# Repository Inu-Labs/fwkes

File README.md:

FWKES[^1] is an open-source NES emulator targeted at 32-bit microcontroller RP2350. It aims to be
precise and cycle-accurate, while still maintaining stable 60 FPS and minimal latency.

*TODO: add demonstration (video, screenshots)*

Features:

- SD card for storing games and files.
- HDMI for video output.
- 3.5mm audio jack for audio output.
- Supports raster effects (mid-scanline writes).
- Emulates NTSC region, i.e. original NES and Famicom (although support for PAL is planned).
- Implements all instruction set of Ricoh 2A03 (MOS 6502), including unofficial instructions and
precise timing.
- Implements all features of PPU (sprite overflow, emphasis bits, ...) and APU.
- Supports **NROM**, **MMC1**, **UNROM** and **MMC3** mappers.
- Supports RP2350-based boards **Raspberry Pi Pico 2**, **Pimoroni Pico Plus 2** and any compatible
board.
- FWKES comes with BIOS that delivers user-friendly interface for loading programs and
  configuration. BIOS can be freely reprogrammed, i.e. can replace it with their own program.
- To allow emulated programs make use of peripherals like SD card, or configure emulator's behavior,
  there is a bridge (hypercall interface) called FWX.

# Building

Although FWKES is aimed at RP2350-based boards, there are development builds for desktop. Desktop
uses SDL3 to handle video, audio and inputs, and it's intended for superficial testing of
non-RP2350-specific aspects.

There is also an ongoing development of debugger, which allows complex testing not only of FWKES
itself, but also emulated programs and games. It's code can be found in the `debugger` branch.

## Dependencies

For RP2350 based, you'll need [ARM GCC compiler toolchain with C11
support](https://developer.arm.com/downloads/-/arm-gnu-toolchain-downloads) and [extracted Pico
SDK](https://github.com/raspberrypi/pico-sdk).

For desktop and debugger versions, only [SDL3](https://www.libsdl.org/) is required to be installed
and usable by CMake. Both GCC and Clang are usable.

For general building, you'll also need [CMake](https://cmake.org/) and [Git](https://git-scm.com/).

Many of listed tools are available in distribution's repositories on Linux.

## Cloning

Since most dependencies are handled using Git submodules, you need to use `git clone --recurse-submodules
https://github.com/Inu-Labs/fwkes.git`. Alternatively, if you already cloned and submodules are not
initialized, you need to run `git submodule update --init --recursive --progress`.

## Raspberry Pi Pico 2

`-DBUILD_RP2350=ON` must be specified when compiling for official Pico 2:

```sh
mkdir build
cd build
cmake -DPICO_SDK_PATH=path_to_extracted_pico-sdk -DCMAKE_BUILD_TYPE=Release -GNinja -DBUILD_RP2350=ON ..
```

## Pimoroni Pico Plus 2

Both `-DBUILD_RP2350=ON` and `-DBUILD_PIMORONI2=ON` must be specified when compiling for Pimoroni 2:

```sh
mkdir build
cd build
cmake -DPICO_SDK_PATH=path_to_extracted_pico-sdk -DCMAKE_BUILD_TYPE=Release -GNinja -DBUILD_RP2350=ON -DBUILD_PIMORONI2=ON ..
```

## Desktop

Pass `-DBUILD_DESKTOP=ON`:

```sh
mkdir build
cd build
cmake -GNinja -DBUILD_DESKTOP=ON -DCMAKE_POLICY_VERSION_MINIMUM=3.5 ..
```

## Debugger

Pass both `-DBUILD_DESKTOP=ON` and `-DBUILD_DEBUGGER=ON`:

```sh
mkdir build
cd build
cmake -GNinja -DBUILD_DESKTOP=ON -DBUILD_DEBUGGER=ON -DCMAKE_POLICY_VERSION_MINIMUM=3.5 ..
```

## Tests (development only)

To build tests, pass `-DBUILD_TESTS=ON` and `-DBUILD_VISUAL_TESTS=ON`:

```sh
mkdir build
cd build
cmake -GNinja -DBUILD_DESKTOP=ON -DBUILD_TESTS=ON -DBUILD_VISUAL_TESTS=ON ..
```

`-DBUILD_VISUAL_TESTS=ON` is required for tests that depend on SDL3.

## Flashing firmware

To flash compiled firmware to RP2350 board, you can either:

- Copy `build/src/rp2350/fwkes-rp2350.uf2` to the board. Note that the board must be booted in the BOOTSEL mode to perform this (otherwise it will not even appear in your file manager).
- Use [picotool](https://github.com/raspberrypi/picotool): `picotool load build/src/rp2350/fwkes-rp2350.uf2 -f && picotool reboot`

A CMake rule for this is planned in the future.

## Electronics, case

*TODO*

# License & Acknowledgement

Code of FWKES is licensed under [GNU GPL v2.0](LICENSE.txt), while hardware (schematics, PCB designs
and 3D models) is licensed under [CERN Open Hardware Licence Version 2 (Strongly
Reciprocal)](./CERN-OHL-S-2.0-LICENSE.txt). This project is a collaborative work of
[inunix3](https://github.com/inunix3) and [kubaa-ma](https://github.com/kubaa-ma).

Software side of FWKES makes use of the following libraries:

- [pico-sdk](https://github.com/raspberrypi/pico-sdk) - not too low-level interaction with RP2350 peripherals.
- [PicoDVI](https://github.com/Wren6991/PicoDVI) - generation of bitbanged DVI signal.
- [LwMEM](https://github.com/MaJerle/lwmem) - allocator interface for embedded systems (used for PSRAM).
- [FatFS](https://elm-chan.org/fsw/ff/) - FAT filesystem implementation for SD card.
- [Unity](https://github.com/ThrowTheSwitch/Unity) - unit-testing framework (used for CPU tests).
- [ImGui](https://github.com/ocornut/imgui.git) and [imgui_club](https://github.com/ocornut/imgui_club.git) - used for debugger UI.
- [ImGuiFileDialog](https://github.com/aiekick/ImGuiFileDialog) - used for open/save file dialog in the debugger.

[^1]: FWKES is pronounced as fukes (/fʌkɛs/). In old Bible printings, you can find that sometimes
    letter U is written as V. So we took it further and doubled it! Although it's not read as double
    U...

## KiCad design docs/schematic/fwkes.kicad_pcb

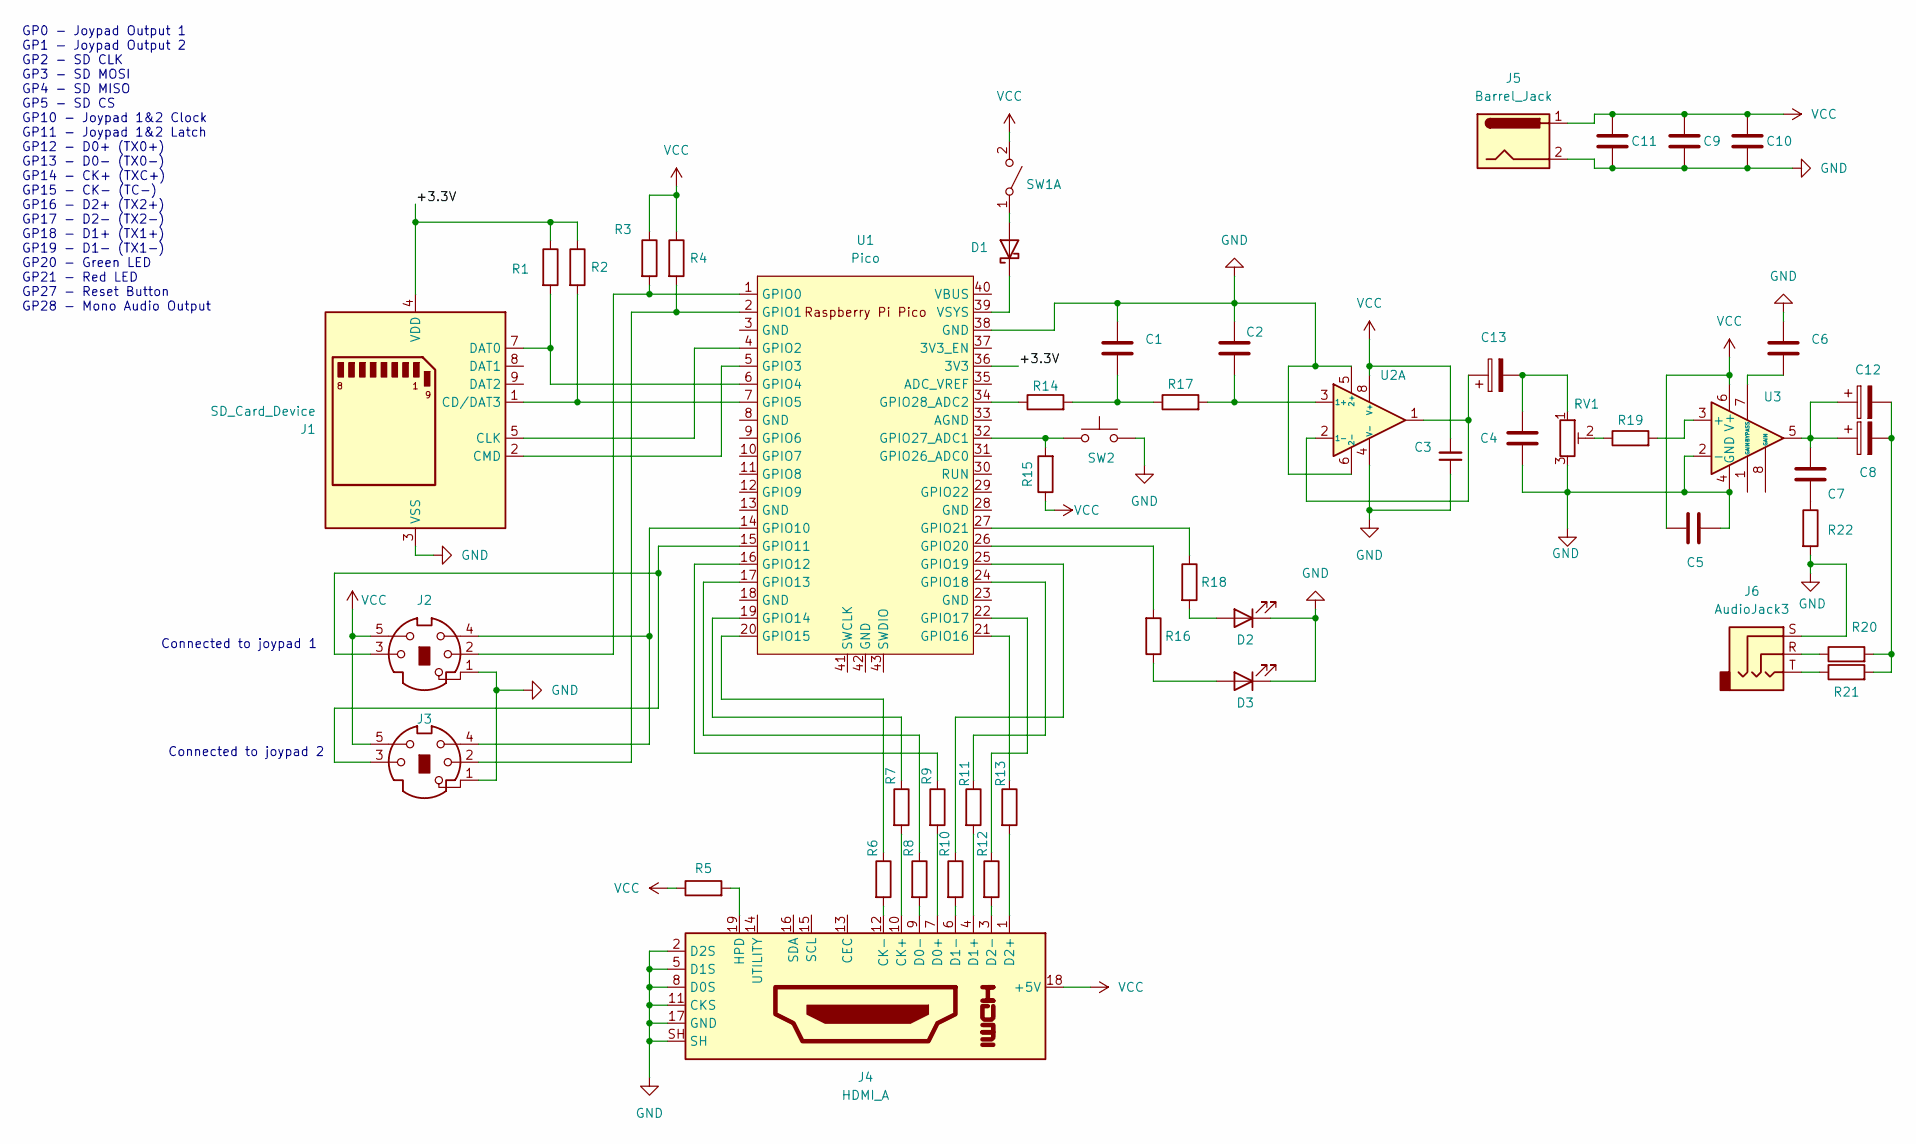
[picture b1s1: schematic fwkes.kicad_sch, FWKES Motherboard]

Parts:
C1, C2: 4n7; C_0603_1608Metric
C3, C4, C5, C6, C7: 100n; C_0603_1608Metric
C8, C10, C12: 100u; C_1210_3225Metric
C9, C13: 10u; C_0603_1608Metric
C11: 1u; C_0603_1608Metric
D1: D_Schottky; D_SOD-123
D2, D3: LED; LED_D3.0mm_Horizontal_O1.27mm_Z2.0mm
J1: SD_Card_Device; SD_Hirose_DM1AA_SF_PEJ82
J2, J3: Mini-DIN-5; MINI_DIN5_KMDGX_5S_BS
J4: HDMI_A; HDMI_A_Amphenol_10029449-x01xLF_Horizontal
J5: Barrel_Jack; BarrelJack_Horizontal
J6: AudioJack3; Jack_3.5mm_Lumberg_1503_03_Horizontal
R1, R2, R3, R4, R5, R15, R22: 10k; R_0603_1608Metric
R6, R7, R8, R9, R10, R11, R12, R13, R16, R18: 220; R_0603_1608Metric
R14, R17: 3k3; R_0603_1608Metric
R19, R20, R21: 1k; R_0603_1608Metric
RV1: 10k; Potentiometer_Bourns_3296Y_Vertical
SW1: SW_DPST_x2; SW_NKK_BB15AH
SW2: SW_Push; SW_NKK_BB15AH
U1: Pico; pico2_socket
U2: LM358; SOIC-8_3.9x4.9mm_P1.27mm
U3: LM386; SOIC-8_3.9x4.9mm_P1.27mm

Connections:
/+3.3V: J1.4 (VDD), R1.1, R2.1, U1.36 (3V3)
GND: C1.1, C2.1, C3.1, C4.2, C5.1, C6.1, C9.2, C10.2, C11.2, D2.1 (K), D3.1 (K), J1.3 (VSS), J1.6 (VSS), J2.1, J3.1, J4.2 (D2S), J4.5 (D1S), J4.8 (D0S), J4.11 (CKS), J4.17 (GND), J4.SH, J5.2, J6.S, R22.2, RV1.3, SW2.2, U1.38 (GND), U2.4 (V-), U2.5 (2+), U2.6 (2-), U3.2 (-), U3.4 (GND)
unnamed: C1.2, R14.2, R17.1
unnamed: C7.2, R22.1
unnamed: C7.1, C8.1, C12.1, U3.5
unnamed: C8.2, C12.2, R20.2, R21.2
unnamed: C4.1, C13.2, RV1.1
unnamed: D1.2 (A), SW1.1 (A)
unnamed: D1.1 (K), U1.39 (VSYS)
unnamed: D2.2 (A), R18.2
unnamed: J1.1 (CD/DAT3), R2.2, U1.7 (GPIO5)
unnamed: J1.5 (CLK), U1.4 (GPIO2)
unnamed: J1.2 (CMD), U1.5 (GPIO3)
unnamed: J1.7 (DAT0), R1.2, U1.6 (GPIO4)
unnamed: J4.10 (CK+), R7.2
unnamed: J4.12 (CK-), R6.2
unnamed: J4.7 (D0+), R9.2
unnamed: J4.9 (D0-), R8.2
unnamed: J4.4 (D1+), R11.2
unnamed: J4.6 (D1-), R10.2
unnamed: J4.1 (D2+), R13.2
unnamed: J4.3 (D2-), R12.2
unnamed: J4.19 (HPD), R5.2
unnamed: J6.R, R20.1
unnamed: J6.T, R21.1
unnamed: R19.1, RV1.2
unnamed: J2.2, R3.2, U1.1 (GPIO0)
unnamed: J3.2, R4.2, U1.2 (GPIO1)
unnamed: J2.4, J3.4, U1.14 (GPIO10)
unnamed: J2.3, J3.3, U1.15 (GPIO11)
unnamed: R9.1, U1.16 (GPIO12)
unnamed: R8.1, U1.17 (GPIO13)
unnamed: R7.1, U1.19 (GPIO14)
unnamed: R6.1, U1.20 (GPIO15)
unnamed: R13.1, U1.21 (GPIO16)
unnamed: R12.1, U1.22 (GPIO17)
unnamed: R11.1, U1.24 (GPIO18)
unnamed: R10.1, U1.25 (GPIO19)
unnamed: R18.1, U1.27 (GPIO21)
unnamed: R15.2, SW2.1, U1.32 (GPIO27_ADC1)
unnamed: R14.1, U1.34 (GPIO28_ADC2)
unnamed: C2.2, R17.2, U2.3 (1+)
unnamed: C13.1, U2.1, U2.2 (1-)
unnamed: R19.2, U3.3 (+)
unnamed: C6.2, U3.7 (BYPASS)
VCC: C3.2, C5.2, C9.1, C10.1, C11.1, J2.5, J3.5, J4.18 (+5V), J5.1, R3.1, R4.1, R5.1, R15.1, SW1.2 (B), U2.8 (V+), U3.6 (V+)

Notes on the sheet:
Connected to joypad 2
Connected to joypad 1
GP0 - Joypad Output 1 GP1 - Joypad Output 2 GP2 - SD CLK GP3 - SD MOSI GP4 - SD MISO GP5 - SD CS GP10 - Joypad 1&2 Clock GP11 - Joypad 1&2 Latch GP12 - D0+ (TX0+) GP13 - D0- (TX0-) GP14 - CK+ (TXC+) GP15 - CK- (TC-) GP16 - D2+ (TX2+) GP17 - D2- (TX2-) GP18 - D1+ (TX1+) GP19 - D1- (TX1-) GP20 - Gree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

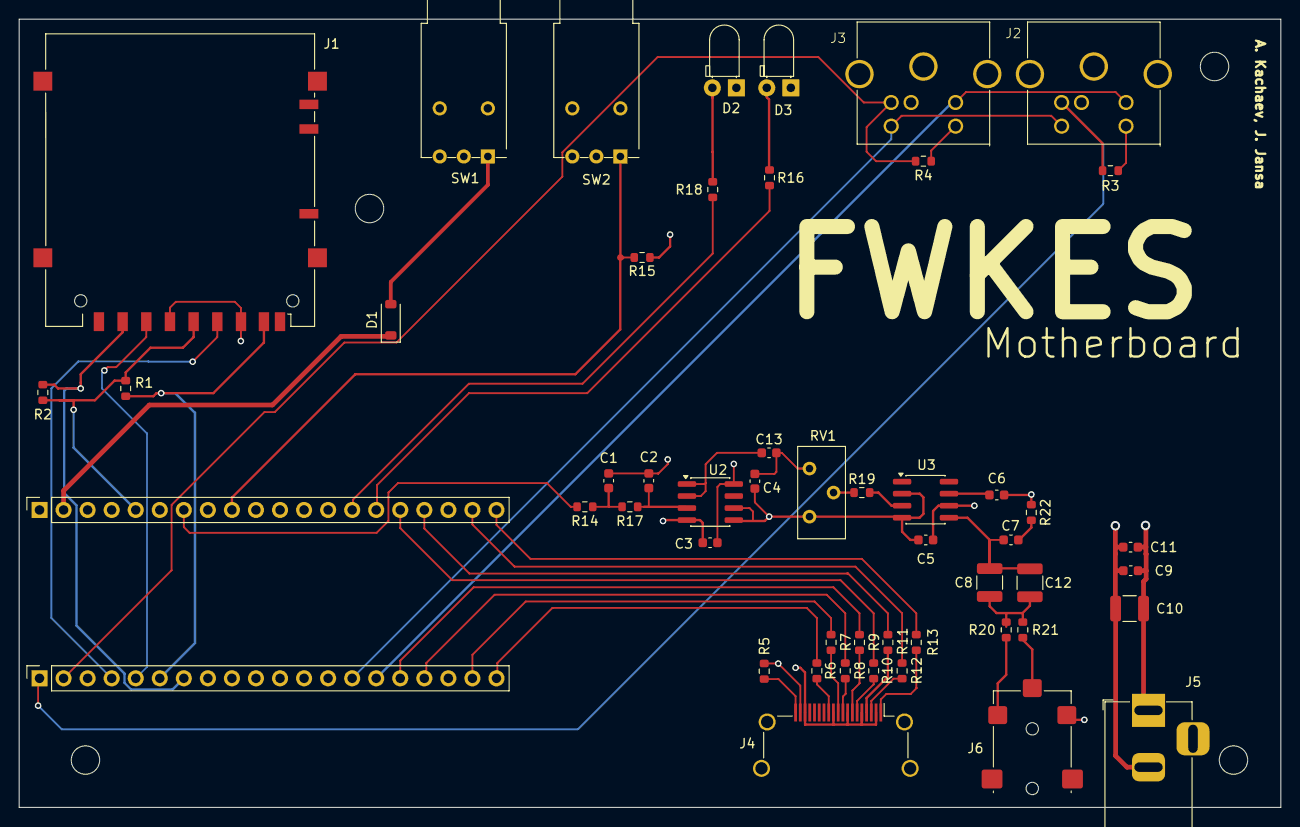
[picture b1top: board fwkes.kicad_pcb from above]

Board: 4 copper layers, 133.2 x 83.2 mm, 50 parts (0 on the bottom side), 48 nets.

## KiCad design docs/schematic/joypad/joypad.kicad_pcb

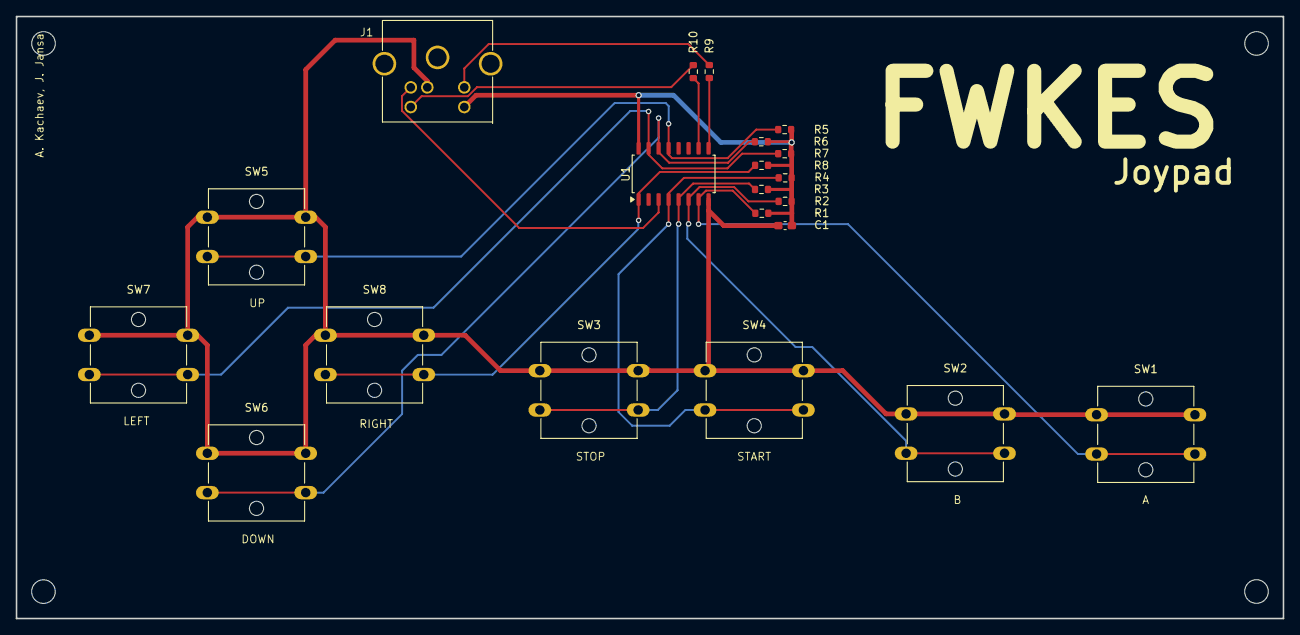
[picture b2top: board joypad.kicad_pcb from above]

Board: 2 copper layers, 161.0 x 76.5 mm, 21 parts (0 on the bottom side), 15 nets.

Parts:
C1: 100nF; C_0603_1608Metric_Pad1.08x0.95mm_HandSolder
J1: Mini-DIN-5; MINI_DIN5_KMDGX_5S_BS
R1, R2, R3, R4, R5, R6, R7, R8, R9, R10: 10K; R_0603_1608Metric
SW1, SW2, SW3, SW4, SW5, SW6, SW7, SW8: SW_Push; SW_SPST_Omron_B3F-40xx
U1: 4021; SOIC-16_4.55x10.3mm_P1.27mm

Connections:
/CLK: J1.4, R10.2
/OUT: J1.2, U1.3 (Q7)
/STROBE: J1.3, R9.2
GND: C1.2, J1.1, SW1.1, SW2.1, SW3.1, SW4.1, SW5.1, SW6.1, SW7.1, SW8.1, U1.8 (VSS)
unnamed: R10.1, U1.10 (CP)
unnamed: R1.1, SW1.2, U1.7 (D0)
unnamed: R2.1, SW2.2, U1.6 (D1)
unnamed: R3.1, SW3.2, U1.5 (D2)
unnamed: R4.1, SW4.2, U1.4 (D3)
unnamed: R5.1, SW5.2, U1.13 (D4)
unnamed: R6.1, SW6.2, U1.14 (D5)
unnamed: R7.1, SW7.2, U1.15 (D6)
unnamed: R8.1, SW8.2, U1.1 (D7)
unnamed: R9.1, U1.9 (PL)
VCC: C1.1, J1.5, R1.2, R2.2, R3.2, R4.2, R5.2, R6.2, R7.2, R8.2, U1.16 (VDD)

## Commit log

2026-05-05 Move files related to SOC to its own branch soc-competition
2026-05-05 Add files from old repo
2026-05-06 add doxyfile
2026-05-06 Documented util.h
2026-05-06 documented trace.h
2026-05-06 edit .gitignore
2026-05-06 remove docs/html
2026-05-06 add docstrings to fwx/private.h
2026-05-07 Document fwx/private.h
2026-05-08 Improve util.h docs
2026-05-08 Documented: PPU
2026-05-09 Document fs.h
2026-05-10 Document joypad.h
2026-05-10 Documented: cpu.h, disk.h
2026-05-10 Fix imgui related compilation error
2026-05-11 Documented: bios
2026-05-12 added extras with BT joypad
2026-05-12 Fixing button arrangement
2026-05-13 Documented: apu.h
2026-05-13 SOC rev. 3
2026-05-14 Documented: joypad.c
2026-05-24 Remove documentation from src/joypad.c
    There's no need for Doxygen documentation in source files, since source files contain implementation
    that is unstable. Source files should contain *plain* comments, that explain what exactly is
    happening, while header files contain general Doxygen documentation, that describes the system from
    high-level perspective, and it should describe the programming interface.
2026-05-24 Add images to README for visual enhancement
    Added images to README for better visual representation.
2026-06-02 Improve trace.h documentation
2026-06-02 Document log.h
2026-06-07 Add images to README for better documentation
    Added images to enhance documentation and provide visual references.
2026-06-07 Add new image to README
    Added an additional image to the README for better visualization.
2026-06-07 Remove unnecessary images from README
    Removed two images from the README file.
2026-06-08 add poster
2026-06-08 edit poster
2026-06-08 export poster to PDF
2026-06-08 fix misspellings in poster
2026-06-08 change Jecna logo to vector one, fix padding in blocks
2026-06-08 add "Building" section in README.md
2026-06-09 update third parties
2026-06-09 sync
2026-06-09 Add docs/html/ to .gitignore
2026-06-13 change svg logo to png
2026-06-17 edit README.md: --recurse-submodules instead of --recursive
